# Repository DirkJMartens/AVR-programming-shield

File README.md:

# AVR-programming-shield
Arduino shield with ZIF socket to program sketches or bootloaders into 28-pin ATMega microcontrollers. 

Usage for sketches: 
===================
1. Install shield onto an Arduino Uno. 
2. Install the target AVR chip into the ZIF socket on the shield. 
3. Connect USB cable between your computer and Arduino Uno. 
4. The (blue) "Power" led should light up on the shield. 
5. Launch the Arduino IDE and load the "ArduinoISP" sketch from the "File - Examples" menu. 
6. Select "Tools - Board" to "Arduino Uno" and "Tools - Port" to the appropriate COM port 
7. Select "Sketch - Upload" to compile and upload the ArduinoISP sketch into your Uno. 
8. The (green) "Heartbeat" led should now fade in and out. 
9. Open the sketch you want to upload into the target AVR chip. 
10. Change the "Tools - Board" to e.g. "Arduino on a breadboard (8 MHz internal clock)". 
11. Change the "Tools - Programmer" to "Arduino as ISP" 
12. Select "Tools - Upload using Programmer" (not Upload). 
13. The sketch will be compiled and uploaded. 
14. During upload, the (amber) "Programming" led should light up. 
15. If the upload was successsful, the (green) "Heartbeat" light should fade in and out again. 
16. If the upload was unsuccesful, the (red) "Error" light should light up. 

Usage for bootloader uploading: 
===============================
1. Repeat steps 1 through 8 above. 
2. Change "Tools - Board" to e.g. "Arduino on a breadboard (8 MHz internal clock)". 
3. Change "Tools - Programmer" to "Arduino as ISP". 
4. Change "Port" to the appropriate port. 
5. Select "Tools - Burn bootloader". 
6. Similar to above, the (amber) "Programming" led should light up during programming. 
7. Upon completion, the (green) "Heartbeat" led should fade or in case of a problem, the (red) "Error" light will light up.

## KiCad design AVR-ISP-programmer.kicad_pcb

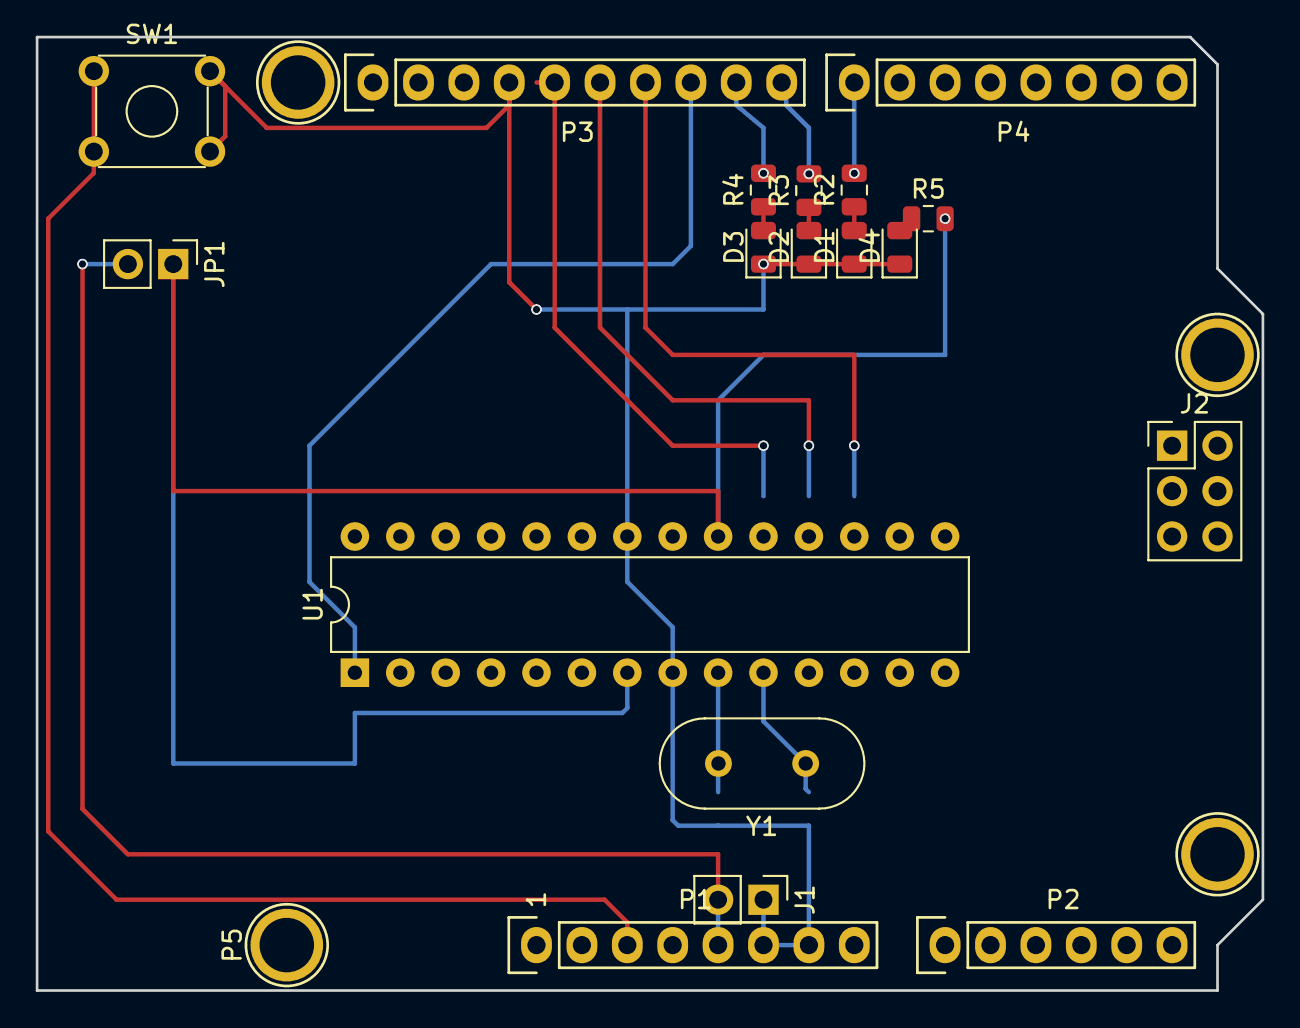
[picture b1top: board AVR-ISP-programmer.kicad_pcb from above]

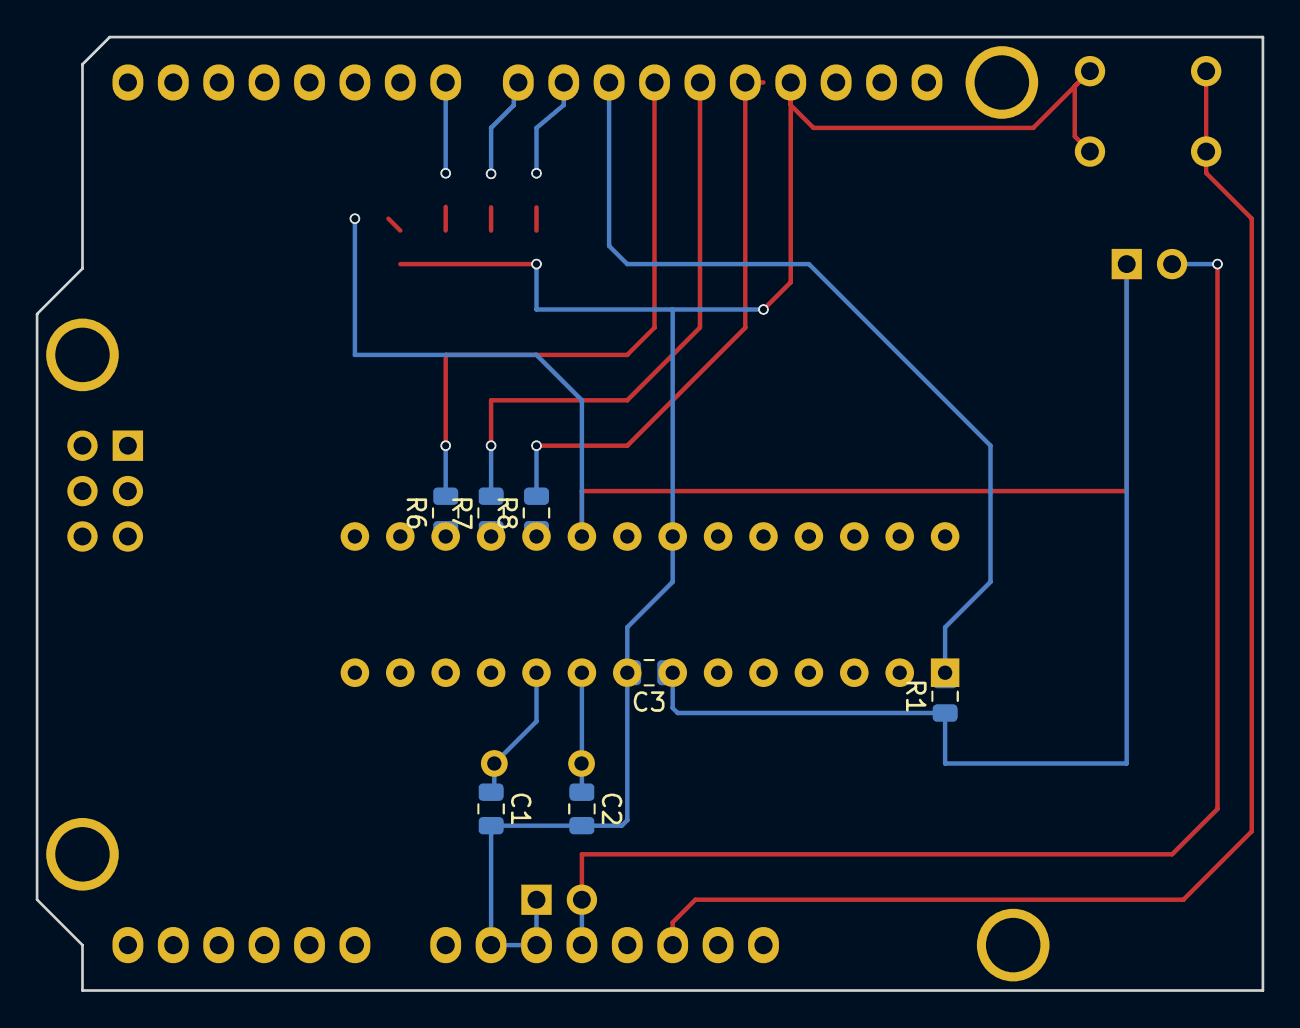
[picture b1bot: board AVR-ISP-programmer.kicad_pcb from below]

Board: 2 copper layers, 68.6 x 53.3 mm, 29 parts (7 on the bottom side), 20 nets.

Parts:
C1, C2: 22p; C_0805_2012Metric
C3: 100n; C_0805_2012Metric
D1: OK (Amber); LED_0805_2012Metric
D2: ERROR (Red); LED_0805_2012Metric
D3: PROGRAM (Green); LED_0805_2012Metric
D4: POWER (Blue); LED_0805_2012Metric
J1: 5V-GND; PinHeader_1x02_P2.54mm_Vertical
J2: ICSP6; PinHeader_2x03_P2.54mm_Vertical
JP1: PWR; PinHeader_1x02_P2.54mm_Vertical
P1: Power; Socket_Strip_Arduino_1x08
P2: Analog; Socket_Strip_Arduino_1x06
P3: Digital; Socket_Strip_Arduino_1x10
P4: Digital; Socket_Strip_Arduino_1x08
P5, P6, P7, P8: CONN_01X01; Arduino_1pin
R1: 10k; R_0805_2012Metric
R2, R3, R4, R5: 2k4; R_0805_2012Metric
R6, R7, R8: 470; R_0805_2012Metric
SW1: RESET; SW_TH_Tactile_Omron_B3F-10xx
U1: ATmega328P-PU; DIP-28_W7.62mm
Y1: 16.934MHz; Crystal_HC49-4H_Vertical

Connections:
+5V: J1.2, JP1.2, P1.5
/7: P4.1, R2.2
/8: P3.10, R3.2
/9(**): P3.9, R4.2
/10(~SS): P3.8, R1.2, U1.1
/11(~MOSI): P3.7, R6.2
/12(MISO): P3.6, R7.2
/13(SCK): P3.5, R8.2
/Reset: P1.3, SW1.1, SW1.3
GND: C1.2, C2.2, C3.2, D1.1, D2.1, D3.1, D4.1, J1.1, P1.6, P1.7, P3.4, SW1.2, SW1.4, U1.8, U1.22
unnamed: C1.1, U1.10, Y1.1
unnamed: C2.1, U1.9, Y1.2
unnamed: C3.1, JP1.1, R1.1, R5.2, U1.7, U1.20
unnamed: D1.2, R2.1
unnamed: D2.2, R3.1
unnamed: D3.2, R4.1
unnamed: D4.2, R5.1
unnamed: R6.1, U1.17
unnamed: R7.1, U1.18
unnamed: R8.1, U1.19
